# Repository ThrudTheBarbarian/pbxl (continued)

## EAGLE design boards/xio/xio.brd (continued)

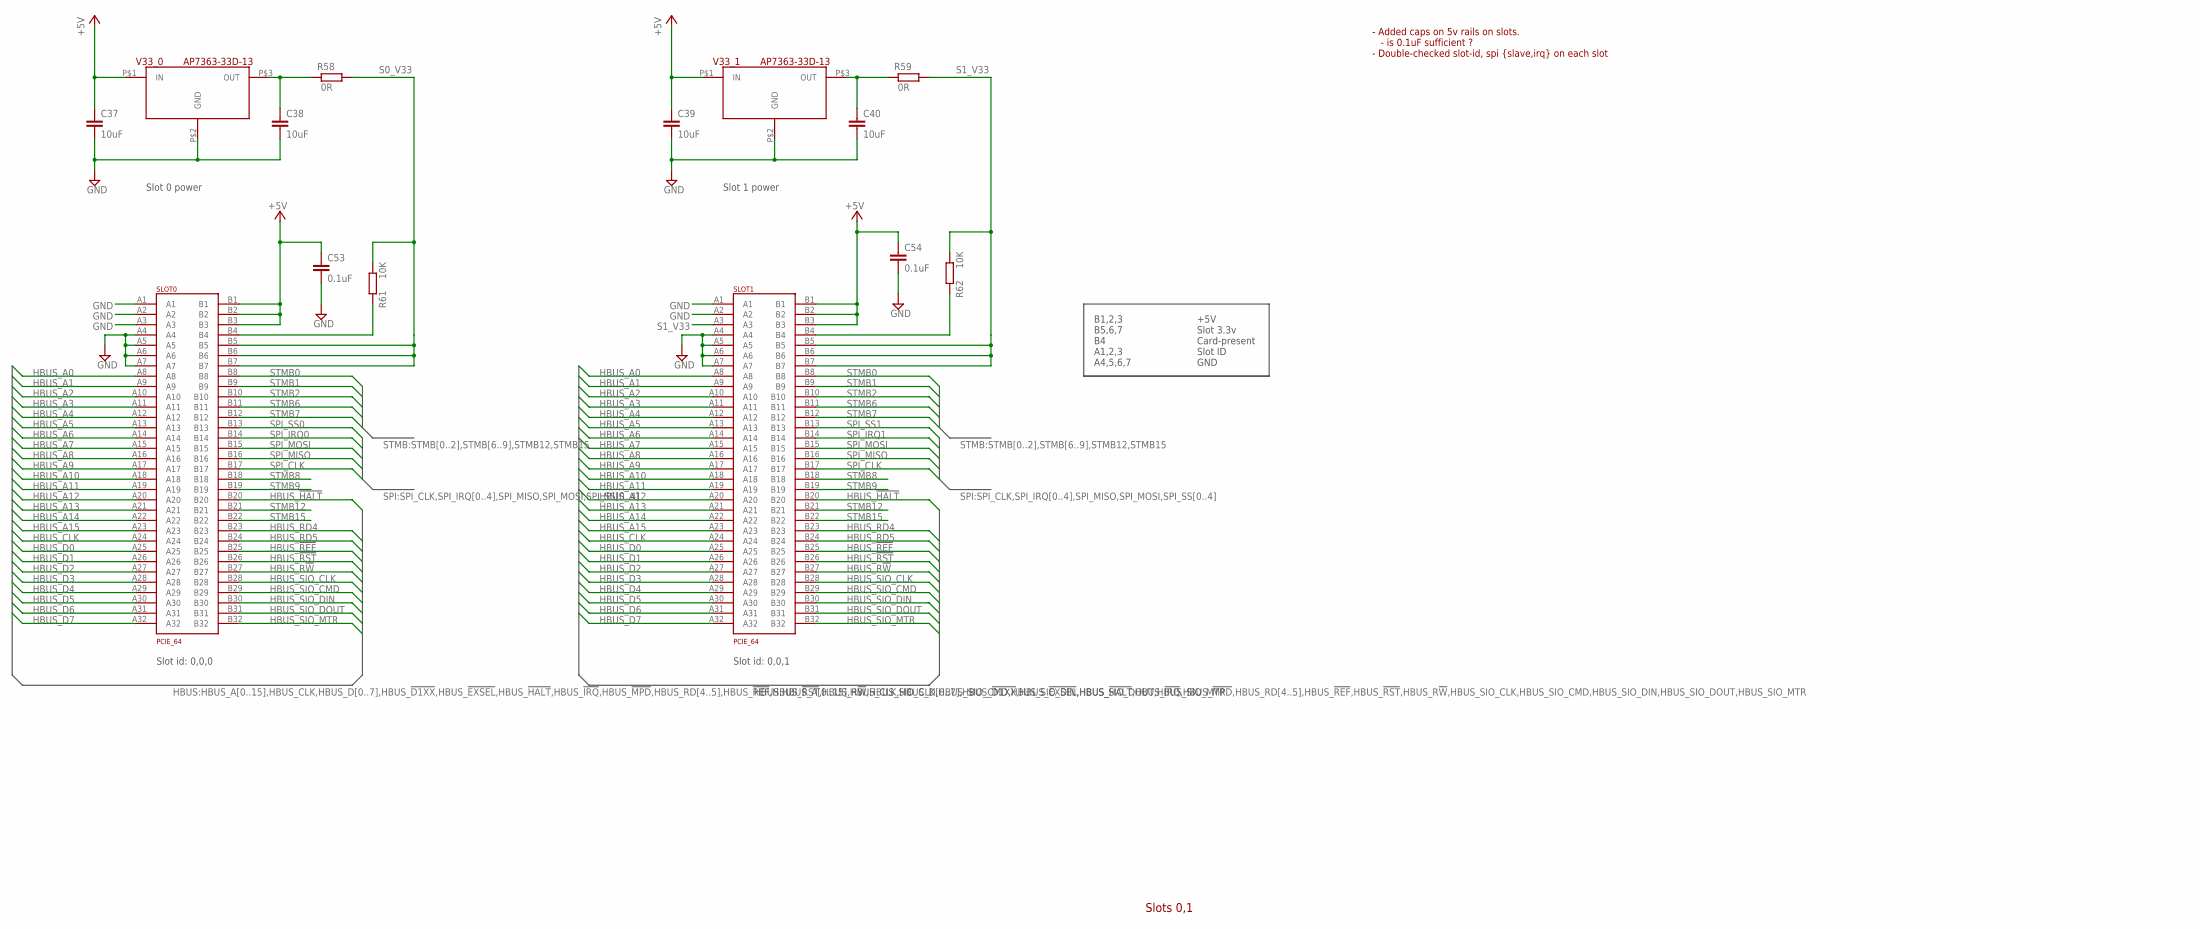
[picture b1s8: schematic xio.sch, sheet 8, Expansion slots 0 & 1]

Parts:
C37, C38, C39, C40: 10uF; C0402K
C53, C54: 0.1uF; C0402K
R58, R59: 0R; R0402
R61, R62: 10K; R0402
SLOT0, SLOT1: PCIE_64; PCI-E_64
V33_0, V33_1: AP7363-33D-13; TO252-3L

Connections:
+5V: C37.1, C39.1, C53.1, C54.1, SLOT0.B1, SLOT0.B2, SLOT0.B3, SLOT1.B1, SLOT1.B2, SLOT1.B3, V33_0.P$1 (IN), V33_1.P$1 (IN); also elsewhere on the board
GND: C37.2, C38.2, C39.2, C40.2, C53.2, C54.2, SLOT0.A1, SLOT0.A2, SLOT0.A3, SLOT0.A4, SLOT0.A5, SLOT0.A6, SLOT0.A7, SLOT1.A1, SLOT1.A2, SLOT1.A4, SLOT1.A5, SLOT1.A6, SLOT1.A7, V33_0.P$2 (GND), V33_1.P$2 (GND); also elsewhere on the board
HBUS_!HALT!: SLOT0.B20, SLOT1.B20; also elsewhere on the board
HBUS_!REF!: SLOT0.B25, SLOT1.B25; also elsewhere on the board
HBUS_!RST!: SLOT0.B26, SLOT1.B26; also elsewhere on the board
HBUS_A0: SLOT0.A8, SLOT1.A8; also elsewhere on the board
HBUS_A1: SLOT0.A9, SLOT1.A9; also elsewhere on the board
HBUS_A2: SLOT0.A10, SLOT1.A10; also elsewhere on the board
HBUS_A3: SLOT0.A11, SLOT1.A11; also elsewhere on the board
HBUS_A4: SLOT0.A12, SLOT1.A12; also elsewhere on the board
HBUS_A5: SLOT0.A13, SLOT1.A13; also elsewhere on the board
HBUS_A6: SLOT0.A14, SLOT1.A14; also elsewhere on the board
HBUS_A7: SLOT0.A15, SLOT1.A15; also elsewhere on the board
HBUS_A8: SLOT0.A16, SLOT1.A16; also elsewhere on the board
HBUS_A9: SLOT0.A17, SLOT1.A17; also elsewhere on the board
HBUS_A10: SLOT0.A18, SLOT1.A18; also elsewhere on the board
HBUS_A11: SLOT0.A19, SLOT1.A19; also elsewhere on the board
HBUS_A12: SLOT0.A20, SLOT1.A20; also elsewhere on the board
HBUS_A13: SLOT0.A21, SLOT1.A21; also elsewhere on the board
HBUS_A14: SLOT0.A22, SLOT1.A22; also elsewhere on the board
HBUS_A15: SLOT0.A23, SLOT1.A23; also elsewhere on the board
HBUS_CLK: SLOT0.A24, SLOT1.A24; also elsewhere on the board
HBUS_D0: SLOT0.A25, SLOT1.A25; also elsewhere on the board
HBUS_D1: SLOT0.A26, SLOT1.A26; also elsewhere on the board
HBUS_D2: SLOT0.A27, SLOT1.A27; also elsewhere on the board
HBUS_D3: SLOT0.A28, SLOT1.A28; also elsewhere on the board
HBUS_D4: SLOT0.A29, SLOT1.A29; also elsewhere on the board
HBUS_D5: SLOT0.A30, SLOT1.A30; also elsewhere on the board
HBUS_D6: SLOT0.A31, SLOT1.A31; also elsewhere on the board
HBUS_D7: SLOT0.A32, SLOT1.A32; also elsewhere on the board
HBUS_R!W!: SLOT0.B27, SLOT1.B27; also elsewhere on the board
HBUS_RD4: SLOT0.B23, SLOT1.B23; also elsewhere on the board
HBUS_RD5: SLOT0.B24, SLOT1.B24; also elsewhere on the board
HBUS_SIO_CLK: SLOT0.B28, SLOT1.B28; also elsewhere on the board
HBUS_SIO_CMD: SLOT0.B29, SLOT1.B29; also elsewhere on the board
HBUS_SIO_DIN: SLOT0.B30, SLOT1.B30; also elsewhere on the board
HBUS_SIO_DOUT: SLOT0.B31, SLOT1.B31; also elsewhere on the board
HBUS_SIO_MTR: SLOT0.B32, SLOT1.B32; also elsewhere on the board
unnamed: R62.2, SLOT1.B4
unnamed: R61.2, SLOT0.B4
unnamed: C38.1, R58.2, V33_0.P$3 (OUT)
unnamed: C40.1, R59.2, V33_1.P$3 (OUT)
S0_V33: R58.1, R61.1, SLOT0.B5, SLOT0.B6, SLOT0.B7
S1_V33: R59.1, R62.1, SLOT1.A3, SLOT1.B5, SLOT1.B6, SLOT1.B7
SPI_CLK: SLOT0.B17, SLOT1.B17; also elsewhere on the board
SPI_IRQ0: SLOT0.B14; also elsewhere on the board
SPI_IRQ1: SLOT1.B14; also elsewhere on the board
SPI_MISO: SLOT0.B16, SLOT1.B16; also elsewhere on the board
SPI_MOSI: SLOT0.B15, SLOT1.B15; also elsewhere on the board
SPI_SS0: SLOT0.B13; also elsewhere on the board
SPI_SS1: SLOT1.B13; also elsewhere on the board
STMB0: SLOT0.B8, SLOT1.B8; also elsewhere on the board
STMB1: SLOT0.B9, SLOT1.B9; also elsewhere on the board
STMB2: SLOT0.B10, SLOT1.B10; also elsewhere on the board
STMB6: SLOT0.B11, SLOT1.B11; also elsewhere on the board
STMB7: SLOT0.B12, SLOT1.B12; also elsewhere on the board
STMB8: SLOT0.B18, SLOT1.B18; also elsewhere on the board
STMB9: SLOT0.B19, SLOT1.B19; also elsewhere on the board
STMB12: SLOT0.B21, SLOT1.B21; also elsewhere on the board
STMB15: SLOT0.B22, SLOT1.B22; also elsewhere on the board

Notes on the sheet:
Slots 0,1
Slot 0 power
Slot 1 power
Slot id: 0,0,0
Slot id: 0,0,1
- Added caps on 5v rails on slots. - is 0.1uF sufficient ? - Double-checked slot-id, spi {slave,irq} on each slot
B1,2,3 B5,6,7 B4 A1,2,3 A4,5,6,7
+5V Slot 3.3v Card-present Slot ID GND

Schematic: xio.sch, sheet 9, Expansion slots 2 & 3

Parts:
C41, C42, C43, C44: 10uF; C0402K
C55, C56: 0.1uF; C0402K
R63, R64: 10K; R0402
R83, R84: 0R; R0402
SLOT2, SLOT3: PCIE_64; PCI-E_64
V33_2, V33_3: AP7363-33D-13; TO252-3L

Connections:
+5V: C41.1, C43.1, C55.1, C56.1, SLOT2.B1, SLOT2.B2, SLOT2.B3, SLOT3.B1, SLOT3.B2, SLOT3.B3, V33_2.P$1 (IN), V33_3.P$1 (IN); also elsewhere on the board
GND: C41.2, C42.2, C43.2, C44.2, C55.2, C56.2, SLOT2.A1, SLOT2.A3, SLOT2.A4, SLOT2.A5, SLOT2.A6, SLOT2.A7, SLOT3.A1, SLOT3.A4, SLOT3.A5, SLOT3.A6, SLOT3.A7, V33_2.P$2 (GND), V33_3.P$2 (GND); also elsewhere on the board
HBUS_!HALT!: SLOT2.B20, SLOT3.B20; also elsewhere on the board
HBUS_!REF!: SLOT2.B25, SLOT3.B25; also elsewhere on the board
HBUS_!RST!: SLOT2.B26, SLOT3.B26; also elsewhere on the board
HBUS_A0: SLOT2.A8, SLOT3.A8; also elsewhere on the board
HBUS_A1: SLOT2.A9, SLOT3.A9; also elsewhere on the board
HBUS_A2: SLOT2.A10, SLOT3.A10; also elsewhere on the board
HBUS_A3: SLOT2.A11, SLOT3.A11; also elsewhere on the board
HBUS_A4: SLOT2.A12, SLOT3.A12; also elsewhere on the board
HBUS_A5: SLOT2.A13, SLOT3.A13; also elsewhere on the board
HBUS_A6: SLOT2.A14, SLOT3.A14; also elsewhere on the board
HBUS_A7: SLOT2.A15, SLOT3.A15; also elsewhere on the board
HBUS_A8: SLOT2.A16, SLOT3.A16; also elsewhere on the board
HBUS_A9: SLOT2.A17, SLOT3.A17; also elsewhere on the board
HBUS_A10: SLOT2.A18, SLOT3.A18; also elsewhere on the board
HBUS_A11: SLOT2.A19, SLOT3.A19; also elsewhere on the board
HBUS_A12: SLOT2.A20, SLOT3.A20; also elsewhere on the board
HBUS_A13: SLOT2.A21, SLOT3.A21; also elsewhere on the board
HBUS_A14: SLOT2.A22, SLOT3.A22; also elsewhere on the board
HBUS_A15: SLOT2.A23, SLOT3.A23; also elsewhere on the board
HBUS_CLK: SLOT2.A24, SLOT3.A24; also elsewhere on the board
HBUS_D0: SLOT2.A25, SLOT3.A25; also elsewhere on the board
HBUS_D1: SLOT2.A26, SLOT3.A26; also elsewhere on the board
HBUS_D2: SLOT2.A27, SLOT3.A27; also elsewhere on the board
HBUS_D3: SLOT2.A28, SLOT3.A28; also elsewhere on the board
HBUS_D4: SLOT2.A29, SLOT3.A29; also elsewhere on the board
HBUS_D5: SLOT2.A30, SLOT3.A30; also elsewhere on the board
HBUS_D6: SLOT2.A31, SLOT3.A31; also elsewhere on the board
HBUS_D7: SLOT2.A32, SLOT3.A32; also elsewhere on the board
HBUS_R!W!: SLOT2.B27, SLOT3.B27; also elsewhere on the board
HBUS_RD4: SLOT2.B23, SLOT3.B23; also elsewhere on the board
HBUS_RD5: SLOT2.B24, SLOT3.B24; also elsewhere on the board
HBUS_SIO_CLK: SLOT2.B28, SLOT3.B28; also elsewhere on the board
HBUS_SIO_CMD: SLOT2.B29, SLOT3.B29; also elsewhere on the board
HBUS_SIO_DIN: SLOT2.B30, SLOT3.B30; also elsewhere on the board
HBUS_SIO_DOUT: SLOT2.B31, SLOT3.B31; also elsewhere on the board
HBUS_SIO_MTR: SLOT2.B32, SLOT3.B32; also elsewhere on the board
unnamed: C42.1, R83.2, V33_2.P$3 (OUT)
unnamed: C44.1, R84.2, V33_3.P$3 (OUT)
unnamed: R63.2, SLOT2.B4
unnamed: R64.2, SLOT3.B4
S2_V33: R63.1, R83.1, SLOT2.A2, SLOT2.B5, SLOT2.B6, SLOT2.B7
S3_V33: R64.1, R84.1, SLOT3.A2, SLOT3.A3, SLOT3.B5, SLOT3.B6, SLOT3.B7
SPI_CLK: SLOT2.B17, SLOT3.B17; also elsewhere on the board
SPI_IRQ2: SLOT2.B14; also elsewhere on the board
SPI_IRQ3: SLOT3.B14; also elsewhere on the board
SPI_MISO: SLOT2.B16, SLOT3.B16; also elsewhere on the board
SPI_MOSI: SLOT2.B15, SLOT3.B15; also elsewhere on the board
SPI_SS2: SLOT2.B13; also elsewhere on the board
SPI_SS3: SLOT3.B13; also elsewhere on the board
STMB0: SLOT2.B8, SLOT3.B8; also elsewhere on the board
STMB1: SLOT2.B9, SLOT3.B9; also elsewhere on the board
STMB2: SLOT2.B10, SLOT3.B10; also elsewhere on the board
STMB6: SLOT2.B11, SLOT3.B11; also elsewhere on the board
STMB7: SLOT2.B12, SLOT3.B12; also elsewhere on the board
STMB8: SLOT2.B18, SLOT3.B18; also elsewhere on the board
STMB9: SLOT2.B19, SLOT3.B19; also elsewhere on the board
STMB12: SLOT2.B21, SLOT3.B21; also elsewhere on the board
STMB15: SLOT2.B22, SLOT3.B22; also elsewhere on the board

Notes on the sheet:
Slot 2 power
Slot 3 power
Slots 2,3
Slot id: 0,1,0
Slot id: 0,1,1
B1,2,3 B5,6,7 B4 A1,2,3 A4,5,6,7
+5V Slot 3.3v Card-present Slot ID GND

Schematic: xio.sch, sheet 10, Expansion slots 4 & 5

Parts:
C45, C46: 10uF; C0402K
C81: 0.1uF; C0402K
R65: 10K; R0402
R85: 0R; R0402
SLOT4: PCIE_64; PCI-E_64
V33_4: AP7363-33D-13; TO252-3L

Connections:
+5V: C45.1, C81.1, SLOT4.B1, SLOT4.B2, SLOT4.B3, V33_4.P$1 (IN); also elsewhere on the board
GND: C45.2, C46.2, C81.2, SLOT4.A2, SLOT4.A3, SLOT4.A4, SLOT4.A5, SLOT4.A6, SLOT4.A7, V33_4.P$2 (GND); also elsewhere on the board
HBUS_!HALT!: SLOT4.B20; also elsewhere on the board
HBUS_!REF!: SLOT4.B25; also elsewhere on the board
HBUS_!RST!: SLOT4.B26; also elsewhere on the board
HBUS_A0: SLOT4.A8; also elsewhere on the board
HBUS_A1: SLOT4.A9; also elsewhere on the board
HBUS_A2: SLOT4.A10; also elsewhere on the board
HBUS_A3: SLOT4.A11; also elsewhere on the board
HBUS_A4: SLOT4.A12; also elsewhere on the board
HBUS_A5: SLOT4.A13; also elsewhere on the board
HBUS_A6: SLOT4.A14; also elsewhere on the board
HBUS_A7: SLOT4.A15; also elsewhere on the board
HBUS_A8: SLOT4.A16; also elsewhere on the board
HBUS_A9: SLOT4.A17; also elsewhere on the board
HBUS_A10: SLOT4.A18; also elsewhere on the board
HBUS_A11: SLOT4.A19; also elsewhere on the board
HBUS_A12: SLOT4.A20; also elsewhere on the board
HBUS_A13: SLOT4.A21; also elsewhere on the board
HBUS_A14: SLOT4.A22; also elsewhere on the board
HBUS_A15: SLOT4.A23; also elsewhere on the board
HBUS_CLK: SLOT4.A24; also elsewhere on the board
HBUS_D0: SLOT4.A25; also elsewhere on the board
HBUS_D1: SLOT4.A26; also elsewhere on the board
HBUS_D2: SLOT4.A27; also elsewhere on the board
HBUS_D3: SLOT4.A28; also elsewhere on the board
HBUS_D4: SLOT4.A29; also elsewhere on the board
HBUS_D5: SLOT4.A30; also elsewhere on the board
HBUS_D6: SLOT4.A31; also elsewhere on the board
HBUS_D7: SLOT4.A32; also elsewhere on the board
HBUS_R!W!: SLOT4.B27; also elsewhere on the board
HBUS_RD4: SLOT4.B23; also elsewhere on the board
HBUS_RD5: SLOT4.B24; also elsewhere on the board
HBUS_SIO_CLK: SLOT4.B28; also elsewhere on the board
HBUS_SIO_CMD: SLOT4.B29; also elsewhere on the board
HBUS_SIO_DIN: SLOT4.B30; also elsewhere on the board
HBUS_SIO_DOUT: SLOT4.B31; also elsewhere on the board
HBUS_SIO_MTR: SLOT4.B32; also elsewhere on the board
unnamed: C46.1, R85.2, V33_4.P$3 (OUT)
unnamed: R65.2, SLOT4.B4
S4_V33: R65.1, R85.1, SLOT4.A1, SLOT4.B5, SLOT4.B6, SLOT4.B7
SPI_CLK: SLOT4.B17; also elsewhere on the board
SPI_IRQ4: SLOT4.B14; also elsewhere on the board
SPI_MISO: SLOT4.B16; also elsewhere on the board
SPI_MOSI: SLOT4.B15; also elsewhere on the board
SPI_SS4: SLOT4.B13; also elsewhere on the board
STMB0: SLOT4.B8; also elsewhere on the board
STMB1: SLOT4.B9; also elsewhere on the board
STMB2: SLOT4.B10; also elsewhere on the board
STMB6: SLOT4.B11; also elsewhere on the board
STMB7: SLOT4.B12; also elsewhere on the board
STMB8: SLOT4.B18; also elsewhere on the board
STMB9: SLOT4.B19; also elsewhere on the board
STMB12: SLOT4.B21; also elsewhere on the board
STMB15: SLOT4.B22; also elsewhere on the board

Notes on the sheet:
Slots 4,5
Slot 4 power
Slot id: 1,0,0
B1,2,3 B5,6,7 B4 A1,2,3 A4,5,6,7
+5V Slot 3.3v Card-present Slot ID GND

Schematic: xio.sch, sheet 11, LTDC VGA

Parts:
D1, D2, D3, D4, D5: BAT54S; SOT23
Q1, Q2: BSS138; SOT23
R10, R28, R42: 71.5K; R0402
R13, R29, R43: 35.7K; R0402
R19, R30, R44: 17.8K; R0402
R20, R31, R45: 8.66K; R0402
R22, R32, R46: 4.37K; R0402
R23, R33, R47: 2.18K; R0402
R24, R34, R48: 1.05K; R0402
R25, R35, R49: 549R; R0402
R50, R51: 1K; R0402
VGA: ICD15S13E4GX00LF; DB15
VGA_BLU: SN74ALVC244PWR; TSSOP20
VGA_GRN: SN74ALVC244PWR; TSSOP20
VGA_RED: SN74ALVC244PWR; TSSOP20
XIO: STM32F429B-XIO; PQFP208

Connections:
+3V3: D3.2 (C2), D4.2 (C2), D5.2 (C2), Q1.1 (G), Q2.1 (G), VGA_BLU.20 (VCC), VGA_GRN.20 (VCC), VGA_RED.20 (VCC); also elsewhere on the board
+5V: D1.2 (C2), D2.2 (C2), R50.1, R51.1; also elsewhere on the board
GND: D1.1 (A1), D2.1 (A1), D3.1 (A1), D4.1 (A1), D5.1 (A1), VGA.5, VGA.6, VGA.7, VGA.8, VGA.10, VGA_BLU.1 (!A_OE!), VGA_BLU.10 (GND), VGA_BLU.19 (!B_OE!), VGA_GRN.1 (!A_OE!), VGA_GRN.10 (GND), VGA_GRN.19 (!B_OE!), VGA_RED.1 (!A_OE!), VGA_RED.10 (GND), VGA_RED.19 (!B_OE!); also elsewhere on the board
LCD_B0: VGA_BLU.2 (A0), XIO.174 (PJ12)
LCD_B1: VGA_BLU.4 (A1), XIO.175 (PJ13)
LCD_B2: VGA_BLU.6 (A2), XIO.176 (PJ14)
LCD_B3: VGA_BLU.8 (A3), XIO.177 (PJ15)
LCD_B4: VGA_BLU.11 (B0), XIO.186 (PK3)
LCD_B5: VGA_BLU.13 (B1), XIO.187 (PK4)
LCD_B6: VGA_BLU.15 (B2), XIO.188 (PK5)
LCD_B7: VGA_BLU.17 (B3), XIO.189 (PK6)
LCD_G0: VGA_GRN.2 (A0), XIO.119 (PJ7)
LCD_G1: VGA_GRN.4 (A1), XIO.120 (PJ8)
LCD_G2: VGA_GRN.6 (A2), XIO.121 (PJ9)
LCD_G3: VGA_GRN.8 (A3), XIO.122 (PJ10)
LCD_G4: VGA_GRN.11 (B0), XIO.123 (PJ11)
LCD_G5: VGA_GRN.13 (B1), XIO.126 (PK0)
LCD_G6: VGA_GRN.15 (B2), XIO.127 (PK1)
LCD_G7: VGA_GRN.17 (B3), XIO.128 (PK2)
LCD_HS: Q2.2 (S), XIO.20 (PI13)
LCD_R0: VGA_RED.2 (A0), XIO.64 (PI15)
LCD_R1: VGA_RED.4 (A1), XIO.65 (PJ0)
LCD_R2: VGA_RED.6 (A2), XIO.66 (PJ1)
LCD_R3: VGA_RED.8 (A3), XIO.67 (PJ2)
LCD_R4: VGA_RED.11 (B0), XIO.68 (PJ3)
LCD_R5: VGA_RED.13 (B1), XIO.69 (PJ4)
LCD_R6: VGA_RED.15 (B2), XIO.95 (PJ5)
LCD_R7: VGA_RED.17 (B3), XIO.118 (PJ6)
LCD_VS: Q1.2 (S), XIO.19 (PI12)
unnamed: R10.2, VGA_RED.18 (Y0)
unnamed: R13.2, VGA_RED.16 (Y1)
unnamed: R19.2, VGA_RED.14 (Y2)
unnamed: R20.2, VGA_RED.12 (Y3)
unnamed: R22.2, VGA_RED.9 (Z0)
unnamed: R23.2, VGA_RED.7 (Z1)
unnamed: R24.2, VGA_RED.5 (Z2)
unnamed: R25.2, VGA_RED.3 (Z3)
unnamed: R35.2, VGA_GRN.3 (Z3)
unnamed: R34.2, VGA_GRN.5 (Z2)
unnamed: R33.2, VGA_GRN.7 (Z1)
unnamed: R32.2, VGA_GRN.9 (Z0)
unnamed: R31.2, VGA_GRN.12 (Y3)
unnamed: R30.2, VGA_GRN.14 (Y2)
unnamed: R29.2, VGA_GRN.16 (Y1)
unnamed: R28.2, VGA_GRN.18 (Y0)
unnamed: R49.2, VGA_BLU.3 (Z3)
unnamed: R48.2, VGA_BLU.5 (Z2)
unnamed: R47.2, VGA_BLU.7 (Z1)
unnamed: R46.2, VGA_BLU.9 (Z0)
unnamed: R45.2, VGA_BLU.12 (Y3)
unnamed: R44.2, VGA_BLU.14 (Y2)
unnamed: R43.2, VGA_BLU.16 (Y1)
unnamed: R42.2, VGA_BLU.18 (Y0)
VGA_B: D3.3 (C1A2), R42.1, R43.1, R44.1, R45.1, R46.1, R47.1, R48.1, R49.1, VGA.3
VGA_G: D4.3 (C1A2), R28.1, R29.1, R30.1, R31.1, R32.1, R33.1, R34.1, R35.1, VGA.2
VGA_HS: D1.3 (C1A2), Q2.3 (D), R51.2, VGA.13
VGA_R: D5.3 (C1A2), R10.1, R13.1, R19.1, R20.1, R22.1, R23.1, R24.1, R25.1, VGA.1
VGA_VS: D2.3 (C1A2), Q1.3 (D), R50.2, VGA.14

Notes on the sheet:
LCD to VGA

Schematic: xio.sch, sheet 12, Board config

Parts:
ARCH_ID: 209-4MS; EDG-04
MEM_ID: 209-2MS; EDG-02
PID: 209-3MS; EDG-03
R6, R7, R8, R9, R14, R15, R16, R17, R18: 47K; R0402
XIO: STM32F429B-XIO; PQFP208

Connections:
+3V3: ARCH_ID.5, ARCH_ID.6, ARCH_ID.7, ARCH_ID.8, MEM_ID.3, MEM_ID.4, PID.4, PID.5, PID.6; also elsewhere on the board
ARCH0: ARCH_ID.1, R9.1, XIO.129 (PG2)
ARCH1: ARCH_ID.2, R8.1, XIO.130 (PG3)
ARCH2: ARCH_ID.3, R7.1, XIO.133 (PG6)
ARCH3: ARCH_ID.4, R6.1, XIO.134 (PG7)
GND: R6.2, R7.2, R8.2, R9.2, R14.2, R15.2, R16.2, R17.2, R18.2; also elsewhere on the board
MEM0: MEM_ID.1, R18.1, XIO.179 (PG10)
MEM1: MEM_ID.2, R17.1, XIO.180 (PG11)
PID0: PID.1, R16.1, XIO.7 (PI8)
PID1: PID.2, R15.1, XIO.13 (PI11)
PID2: PID.3, R14.1, XIO.21 (PI14)

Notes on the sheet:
Architecture selection
Peripheral-ID selection
Memory-emulation selection
Board config

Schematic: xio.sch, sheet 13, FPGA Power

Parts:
C36, C47, C48, C49, C50, C51, C58, C59, C74, C75, C77, C80, C84, C87: 4.7uF; C0402K
C52, C73, C76, C78, C79, C82, C83, C85, C86, C88: 0.47uF; C0402K
C93: 10uF; C0402K
C95: 0.1uF; C0402K
R67: 120R; R0402
VREG1_2: LD1117; SOT223
XLX-: 6SLX9TQG144; TQ144

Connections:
1.2V: C36.1, C73.1, C74.1, C75.1, C93.1, R67.1, VREG1_2.2 (VOUT), VREG1_2.4 (TAB), XLX-.P19 (VCCINT), XLX-.P28 (VCCINT), XLX-.P52 (VCCINT), XLX-.P89 (VCCINT), XLX-.P128 (VCCINT)
+3V3: C47.1, C48.1, C49.1, C50.1, C51.1, C52.1, C58.1, C59.1, C76.1, C77.1, C78.1, C79.1, C80.1, C82.1, C83.1, C84.1, C85.1, C86.1, C87.1, C88.1, C95.1, VREG1_2.3 (VIN), XLX-.P20 (VCCAUX), XLX-.P36 (VCCAUX), XLX-.P53 (VCCAUX), XLX-.P90 (VCCAUX), XLX-.P129 (VCCAUX); also elsewhere on the board
GND: C36.2, C47.2, C48.2, C49.2, C50.2, C51.2, C52.2, C58.2, C59.2, C73.2, C74.2, C75.2, C76.2, C77.2, C78.2, C79.2, C80.2, C82.2, C83.2, C84.2, C85.2, C86.2, C87.2, C88.2, C93.2, C95.2, R67.2, VREG1_2.1 (GND), XLX-.P3 (GND), XLX-.P13 (GND), XLX-.P25 (GND), XLX-.P49 (GND), XLX-.P54 (GND), XLX-.P68 (GND), XLX-.P77 (GND), XLX-.P91 (GND), XLX-.P96 (GND), XLX-.P108 (GND), XLX-.P113 (GND), XLX-.P130 (GND), XLX-.P136 (GND); also elsewhere on the board

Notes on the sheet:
VccAux bypass caps
VccInt bypass caps
VccO bank 0
VccO bank 1
VccO bank 2
VccO bank 3
Bypass cap number and capacitance taken from ug393

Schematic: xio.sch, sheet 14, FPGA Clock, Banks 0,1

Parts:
C35: 0.01uF; C0402K
J1: 12401598E4#2A; AMPHENOL_12401598E4#2A
JP1: PINHD-2X8; 2X08
JP2: PINHD-2X7; 2X07
OSC1: ASEMB-50.000MHZ-LC-T; OSC_3.2X2.5MM
R78, R79, R80, R81, R82, R86, R87: 33R; R0402
XLX-: 6SLX9TQG144; TQ144

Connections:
+3V3: C35.1, JP1.15, JP2.14, OSC1.4 (VCC), XLX-.P76 (VCCO_1), XLX-.P86 (VCCO_1), XLX-.P103 (VCCO_1), XLX-.P122 (VCCO_0), XLX-.P125 (VCCO_0), XLX-.P135 (VCCO_0); also elsewhere on the board
FBUS0: JP1.14, XLX-.P127 (IO_L36P_GCLK15_0)
FBUS1: JP1.12, XLX-.P126 (IO_L36N_GCLK14_0)
FBUS2: JP1.10, XLX-.P123 (IO_L37N_GCLK12_0)
FBUS3: JP1.8, XLX-.P121 (IO_L62P_0)
FBUS4: JP1.6, XLX-.P120 (IO_L62N_VREF_0)
FBUS5: JP1.4, XLX-.P119 (IO_L63P_SCP7_0)
FBUS6: JP1.2, XLX-.P118 (IO_L63N_SCP6_0)
FBUS7: JP1.13, XLX-.P117 (IO_L64P_SCP5_0)
FBUS8: JP1.11, XLX-.P116 (IO_L64N_SCP4_0)
FBUS9: JP1.9, XLX-.P115 (IO_L65P_SCP3_0)
FBUS10: JP1.7, XLX-.P114 (IO_L65N_SCP2_0)
FBUS11: JP1.5, XLX-.P112 (IO_L66P_SCP1_0)
FBUS12: JP1.3, XLX-.P111 (IO_L66N_SCP0_0)
FBUS13: JP2.1, XLX-.P105 (IO_L1P_1)
FBUS14: JP2.3, XLX-.P104 (IO_L1N_VREF_1)
FBUS15: JP2.5, XLX-.P99 (IO_L33N_1)
FBUS16: JP2.7, XLX-.P98 (IO_L34P_1)
FBUS17: JP2.9, XLX-.P97 (IO_L34N_1)
FBUS18: JP2.11, XLX-.P95 (IO_L40P_GCLK11_1)
FBUS19: JP2.2, XLX-.P88 (IO_L42P_GCLK7_1)
FBUS20: JP2.4, XLX-.P87 (IO_L42N_GCLK6_TRDY1_1)
FBUS21: JP2.6, XLX-.P85 (IO_L43P_GCLK5_1)
FBUS22: JP2.8, XLX-.P84 (IO_L43N_GCLK4_1)
FBUS23: JP2.10, XLX-.P83 (IO_L45P_1)
FBUS24: JP2.12, XLX-.P82 (IO_L45N_1)
GND: C35.2, J1.A1 (GND), J1.A12 (GND), J1.B1 (GND), J1.B12 (GND), J1.SH1 (SHIELD), J1.SH2 (SHIELD), J1.SH3 (SHIELD), J1.SH4 (SHIELD), JP1.1, JP1.16, JP2.13, OSC1.2 (GND), XLX-.P144 (IO_L1P_HSWAPEN_0); also elsewhere on the board
HBUS_DDIR: XLX-.P143 (IO_L1N_VREF_0); also elsewhere on the board
LX_CLK: OSC1.3 (OUT), XLX-.P124 (IO_L37P_GCLK13_0)
LX_RC_N: J1.B10 (SSRXN1), XLX-.P131 (IO_L35N_GCLK16_0)
LX_RC_P: J1.B11 (SSRXP1), XLX-.P132 (IO_L35P_GCLK17_0)
LX_RD_N: J1.B2 (SSTXP2), XLX-.P141 (IO_L2N_0)
LX_RD_P: J1.B3 (SSTXN2), XLX-.P142 (IO_L2P_0)
LX_TC_N: J1.A6 (DP1), XLX-.P137 (IO_L4N_0)
LX_TC_P: J1.A7 (DN1), XLX-.P138 (IO_L4P_0)
LX_TD0_N: J1.A2 (SSTXP1), XLX-.P133 (IO_L34N_GCLK18_0)
LX_TD0_P: J1.A3 (SSTXN1), XLX-.P134 (IO_L34P_GCLK19_0)
LX_TD1_N: J1.A10 (SSRXN2), XLX-.P139 (IO_L3N_0)
LX_TD1_P: J1.A11 (SSRXP2), XLX-.P140 (IO_L3P_0)
unnamed: R82.1, XLX-.P92 (IO_L41N_GCLK8_1)
unnamed: R81.1, XLX-.P94 (IO_L40N_GCLK10_1)
unnamed: R79.1, XLX-.P100 (IO_L33P_1)
unnamed: R78.1, XLX-.P101 (IO_L32N_1)
unnamed: R80.1, XLX-.P75 (IO_L74P_AWAKE_1)
unnamed: R86.1, XLX-.P81 (IO_L46P_1)
unnamed: R87.1, XLX-.P79 (IO_L47P_1)
XSPI_1_MISO: R80.2; also elsewhere on the board
XSPI_1_MOSI: XLX-.P74 (IO_L74N_DOUT_BUSY_1); also elsewhere on the board
XSPI_1_SCK: XLX-.P78 (IO_L47N_1); also elsewhere on the board
XSPI_3_MISO: XLX-.P93 (IO_L41P_GCLK9_IRDY1_1); also elsewhere on the board
XSPI_3_MOSI: R82.2; also elsewhere on the board
XSPI_3_SCK: R81.2; also elsewhere on the board
XSPI_5_MISO: XLX-.P80 (IO_L46N_1); also elsewhere on the board
XSPI_5_MOSI: R87.2; also elsewhere on the board
XSPI_5_SCK: R86.2; also elsewhere on the board
XSPI_6_MISO: XLX-.P102 (IO_L32P_1); also elsewhere on the board
XSPI_6_MOSI: R79.2; also elsewhere on the board
XSPI_6_SCK: R78.2; also elsewhere on the board

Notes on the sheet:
INH can be left floating for normal operation
Trace thickness Prepreg thickness Trace width Inter-trace spacing Prepreg dielectric Differential impedance
0.035 mm 0.12 mm 10 mil 7 mil 4.4 90.5 ohms
USB3 connections
Bank 0
Bank 1
Clock
FPGA Clock, Banks 0 & 1

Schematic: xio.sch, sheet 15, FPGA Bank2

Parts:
A_MUX: TS3A27518EPWR; TSSOP24
C25, C30, C96: 0.1uF; C0402K
C97: 1uF; C0402K
FPGA_CFG: W25Q80DVSNIG; SOIC8_150MIL
FPGA_DONE: LTST-C191KFKT; CHIPLED_0603
FPGA_PROG: XILINX-JTAG; 332-14
R52: 680R; R0402
R54, R55, R57: 2.4K; R0402
R60, R66, R70, R71: 4.7K; R0402
R68, R69: 33R; R0402
RESET_XLX: 1825910-6; TACTILE-PTH
XLX-: 6SLX9TQG144; TQ144

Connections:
+3V3: A_MUX.8 (VCC), A_MUX.16 (NO6), A_MUX.18 (NO5), C25.1, C96.1, C97.1, FPGA_CFG.8 (VCC), FPGA_PROG.2 (VREF), R52.1, R54.2, R55.2, R57.2, R60.2, R66.2, XLX-.P42 (VCCO_2), XLX-.P63 (VCCO_2), XLX-.P69 (IO_L1N_M0_CMPMISO_2); also elsewhere on the board
FLASH_CLK: A_MUX.2 (NC1), R68.2
FLASH_CS: A_MUX.21 (NC4), R57.1, XLX-.P38 (IO_L65N_CSO_B_2)
FLASH_D0: A_MUX.1 (NC2), R69.2
FLASH_D1: A_MUX.23 (NC3), XLX-.P65 (IO_L3P_D0_DIN_MISO_MISO1_2)
FLASH_D2: A_MUX.19 (NC5), R55.1, XLX-.P62 (IO_L12P_D1_MISO2_2)
FLASH_D3: A_MUX.22 (NC6), R54.1, XLX-.P61 (IO_L12N_D2_MISO3_2)
GND: A_MUX.5 (GND), A_MUX.17 (NO4), C25.2, C30.2, C96.2, C97.2, FPGA_CFG.4 (VSS), FPGA_DONE.C, FPGA_PROG.1 (GND), FPGA_PROG.3 (GND), FPGA_PROG.5 (GND), FPGA_PROG.7 (GND), FPGA_PROG.9 (GND), FPGA_PROG.11 (GND), FPGA_PROG.13 (GND), R70.2, R71.2, RESET_XLX.1, RESET_XLX.2, XLX-.P60 (IO_L13P_M1_2), XLX-.P73 (SUSPEND); also elsewhere on the board
HBUS_!CCTL!: XLX-.P40 (IO_L64N_D9_2); also elsewhere on the board
HBUS_!REF!: XLX-.P44 (IO_L62P_D5_2); also elsewhere on the board
HBUS_!RST!: XLX-.P45 (IO_L49N_D4_2); also elsewhere on the board
HBUS_!S4!: XLX-.P47 (IO_L48N_RDWR_B_VREF_2); also elsewhere on the board
HBUS_!S5!: XLX-.P48 (IO_L48P_D7_2); also elsewhere on the board
HBUS_R!W!: XLX-.P46 (IO_L49P_D3_2); also elsewhere on the board
HBUS_RD4: XLX-.P41 (IO_L64P_D8_2); also elsewhere on the board
HBUS_RD5: XLX-.P43 (IO_L62N_D6_2); also elsewhere on the board
HBUS_SIO_CLK: XLX-.P50 (IO_L31N_GCLK30_D15_2); also elsewhere on the board
HBUS_SIO_CMD: XLX-.P51 (IO_L31P_GCLK31_D14_2); also elsewhere on the board
HBUS_SIO_DIN: XLX-.P55 (IO_L30N_GCLK0_USERCCLK_2); also elsewhere on the board
HBUS_SIO_DOUT: XLX-.P56 (IO_L30P_GCLK1_D13_2); also elsewhere on the board
HBUS_SIO_MTR: XLX-.P57 (IO_L14N_D12_2); also elsewhere on the board
unnamed: A_MUX.4 (COM1), FPGA_CFG.6 (SCK)
unnamed: FPGA_DONE.A, R52.2, XLX-.P71 (DONE_2)
unnamed: R60.1, XLX-.P39 (IO_L65P_INIT_B_2)
unnamed: C30.1, R66.1, RESET_XLX.3, RESET_XLX.4, XLX-.P37 (PROGRAM_B_2)
unnamed: FPGA_PROG.4 (SS/PROG/TMS), XLX-.P107 (TMS)
unnamed: FPGA_PROG.6 (SCK/CCLK/TCK), XLX-.P109 (TCK)
unnamed: FPGA_PROG.8 (MISO/DONE/TDO), XLX-.P106 (TDO)
unnamed: FPGA_PROG.10 (MOSI/DIN/TDI), XLX-.P110 (TDI)
unnamed: A_MUX.6 (COM2), FPGA_CFG.5 (MOSI)
unnamed: A_MUX.7 (COM3), FPGA_CFG.2 (MISO)
unnamed: A_MUX.9 (COM4), FPGA_CFG.1 (SSEL)
unnamed: A_MUX.10 (COM5), FPGA_CFG.3 (#WP/IO2)
unnamed: A_MUX.12 (COM6), FPGA_CFG.7 (#HOLD/IO3)
unnamed: R68.1, XLX-.P70 (IO_L1P_CCLK_2)
unnamed: R69.1, XLX-.P64 (IO_L3N_MOSI_CSI_B_MISO0_2)
unnamed: A_MUX.20 (!EN!), R70.1
SPI_CLK: A_MUX.11 (NO1); also elsewhere on the board
SPI_MISO: A_MUX.15 (NO3); also elsewhere on the board
SPI_MOSI: A_MUX.13 (NO2); also elsewhere on the board
SPI_MUX_IN: A_MUX.14 (IN2), A_MUX.24 (IN1), R71.1; also elsewhere on the board

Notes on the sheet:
Green LED
Bank 2 / Config
CMPCS_B for Xilinx use only
Trace thickness Prepreg thickness Trace width Prepreg dielectric Trace impedance
0.035 mm 0.12 mm 8 mil 4.4 50.2 ohms
FLASH_CLK impedance matching
Place 33R resistors close to FPGA pins
Default (NC) is that the FPGA has control over the SPI flash. If the STM pulls XIO_MUX_EN high, it gains control
Pins 12,14 are NC

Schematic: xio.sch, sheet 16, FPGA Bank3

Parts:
C57, C60, C61, C62, C63, C64, C65, C66, C67, C68, C69, C70, C71, C72: 0.1uF; C0402K
CARTRIDGE: A8_CART
LVL_AHI: SN74LVC8T245; TSSOP24
LVL_ALO: SN74LVC8T245; TSSOP24
LVL_CLK: 74LVCH1T45GW,125; SOT363
LVL_D: SN74LVC8T245; TSSOP24
LVL_RD4, LVL_RD5: 74LVCH1T45GW,125; SOT363
LVL_RW: 74LVCH1T45GW,125; SOT363
XLX-: 6SLX9TQG144; TQ144

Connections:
+3V3: C57.1, C60.1, C61.1, C62.1, C63.1, C64.1, C65.1, LVL_AHI.1 (VCCA), LVL_AHI.2 (DIR), LVL_ALO.1 (VCCA), LVL_ALO.2 (DIR), LVL_CLK.1 (VCCA), LVL_CLK.5 (DIR), LVL_D.1 (VCCA), LVL_RD4.5 (DIR), LVL_RD4.6 (VCCB), LVL_RD5.5 (DIR), LVL_RD5.6 (VCCB), LVL_RW.1 (VCCA), LVL_RW.5 (DIR), XLX-.P4 (VCCO_3), XLX-.P18 (VCCO_3), XLX-.P31 (VCCO_3); also elsewhere on the board
+5V: C66.1, C67.1, C68.1, C69.1, C70.1, C71.1, C72.1, CARTRIDGE.P13 (VCC5), LVL_AHI.23 (VCCB), LVL_AHI.24 (VCCB), LVL_ALO.23 (VCCB), LVL_ALO.24 (VCCB), LVL_CLK.6 (VCCB), LVL_D.23 (VCCB), LVL_D.24 (VCCB), LVL_RD4.1 (VCCA), LVL_RD5.1 (VCCA), LVL_RW.6 (VCCB); also elsewhere on the board
CBUS_!CCTL!: CARTRIDGE.P15 (!CCTL!), LVL_AHI.16 (B6)
CBUS_!S4!: CARTRIDGE.P1 (!S4!), LVL_AHI.15 (B7)
CBUS_!S5!: CARTRIDGE.P12 (!S5!), LVL_AHI.14 (B8)
CBUS_A0: CARTRIDGE.P5 (A0), LVL_ALO.21 (B1)
CBUS_A1: CARTRIDGE.P4 (A1), LVL_ALO.20 (B2)
CBUS_A2: CARTRIDGE.P3 (A2), LVL_ALO.19 (B3)
CBUS_A3: CARTRIDGE.P2 (A3), LVL_ALO.18 (B4)
CBUS_A4: CARTRIDGE.PC (A4), LVL_ALO.17 (B5)
CBUS_A5: CARTRIDGE.PD (A5), LVL_ALO.16 (B6)
CBUS_A6: CARTRIDGE.PE (A6), LVL_ALO.15 (B7)
CBUS_A7: CARTRIDGE.PF (A7), LVL_ALO.14 (B8)
CBUS_A8: CARTRIDGE.PH (A8), LVL_AHI.21 (B1)
CBUS_A9: CARTRIDGE.PJ (A9), LVL_AHI.20 (B2)
CBUS_A10: CARTRIDGE.PP (A10), LVL_AHI.19 (B3)
CBUS_A11: CARTRIDGE.PN (A11), LVL_AHI.18 (B4)
CBUS_A12: CARTRIDGE.PK (A12), LVL_AHI.17 (B5)
CBUS_B02: CARTRIDGE.PS (B02), LVL_CLK.4 (B)
CBUS_D0: CARTRIDGE.P10 (D0), LVL_D.21 (B1)
CBUS_D1: CARTRIDGE.P9 (D1), LVL_D.20 (B2)
CBUS_D2: CARTRIDGE.P8 (D2), LVL_D.19 (B3)
CBUS_D3: CARTRIDGE.PL (D3), LVL_D.18 (B4)
CBUS_D4: CARTRIDGE.P6 (D4), LVL_D.17 (B5)
CBUS_D5: CARTRIDGE.P7 (D5), LVL_D.16 (B6)
CBUS_D6: CARTRIDGE.P11 (D6), LVL_D.15 (B7)
CBUS_D7: CARTRIDGE.PM (D7), LVL_D.14 (B8)
CBUS_R/!W!: CARTRIDGE.PR (R/!W!), LVL_RW.4 (B)
GND: C57.2, C60.2, C61.2, C62.2, C63.2, C64.2, C65.2, C66.2, C67.2, C68.2, C69.2, C70.2, C71.2, C72.2, CARTRIDGE.PB (GND), LVL_AHI.11 (GND), LVL_AHI.12 (GND), LVL_AHI.13 (GND), LVL_AHI.22 (!OE!), LVL_ALO.11 (GND), LVL_ALO.12 (GND), LVL_ALO.13 (GND), LVL_ALO.22 (!OE!), LVL_CLK.2 (GND), LVL_D.11 (GND), LVL_D.12 (GND), LVL_D.13 (GND), LVL_D.22 (!OE!), LVL_RD4.2 (GND), LVL_RD5.2 (GND), LVL_RW.2 (GND); also elsewhere on the board
HBUS_!CCTL!: LVL_AHI.8 (A6); also elsewhere on the board
HBUS_!S4!: LVL_AHI.9 (A7); also elsewhere on the board
HBUS_!S5!: LVL_AHI.10 (A8); also elsewhere on the board
HBUS_A0: LVL_ALO.3 (A1), XLX-.P22 (IO_L42P_GCLK25_TRDY2_3); also elsewhere on the board
HBUS_A1: LVL_ALO.4 (A2), XLX-.P21 (IO_L42N_GCLK24_3); also elsewhere on the board
HBUS_A2: LVL_ALO.5 (A3), XLX-.P17 (IO_L43P_GCLK23_3); also elsewhere on the board
HBUS_A3: LVL_ALO.6 (A4), XLX-.P16 (IO_L43N_GCLK22_IRDY2_3); also elsewhere on the board
HBUS_A4: LVL_ALO.7 (A5), XLX-.P15 (IO_L44P_GCLK21_3); also elsewhere on the board
HBUS_A5: LVL_ALO.8 (A6), XLX-.P14 (IO_L44N_GCLK20_3); also elsewhere on the board
HBUS_A6: LVL_ALO.9 (A7), XLX-.P12 (IO_L49P_3); also elsewhere on the board
HBUS_A7: LVL_ALO.10 (A8), XLX-.P11 (IO_L49N_3); also elsewhere on the board
HBUS_A8: LVL_AHI.3 (A1), XLX-.P29 (IO_L36N_3); also elsewhere on the board
HBUS_A9: LVL_AHI.4 (A2), XLX-.P27 (IO_L37P_3); also elsewhere on the board
HBUS_A10: LVL_AHI.5 (A3), XLX-.P26 (IO_L37N_3); also elsewhere on the board
HBUS_A11: LVL_AHI.6 (A4), XLX-.P24 (IO_L41P_GCLK27_3); also elsewhere on the board
HBUS_A12: LVL_AHI.7 (A5), XLX-.P23 (IO_L41N_GCLK26_3); also elsewhere on the board
HBUS_A13: XLX-.P33 (IO_L2P_3); also elsewhere on the board
HBUS_A14: XLX-.P32 (IO_L2N_3); also elsewhere on the board
HBUS_A15: XLX-.P30 (IO_L36P_3); also elsewhere on the board
HBUS_CLK: LVL_CLK.3 (A), XLX-.P34 (IO_L1N_VREF_3); also elsewhere on the board
HBUS_D0: LVL_D.3 (A1), XLX-.P10 (IO_L50P_3); also elsewhere on the board
HBUS_D1: LVL_D.4 (A2), XLX-.P9 (IO_L50N_3); also elsewhere on the board
HBUS_D2: LVL_D.5 (A3), XLX-.P8 (IO_L51P_3); also elsewhere on the board
HBUS_D3: LVL_D.6 (A4), XLX-.P7 (IO_L51N_3); also elsewhere on the board
HBUS_D4: LVL_D.7 (A5), XLX-.P6 (IO_L52P_3); also elsewhere on the board
HBUS_D5: LVL_D.8 (A6), XLX-.P5 (IO_L52N_3); also elsewhere on the board
HBUS_D6: LVL_D.9 (A7), XLX-.P2 (IO_L83P_3); also elsewhere on the board
HBUS_D7: LVL_D.10 (A8), XLX-.P1 (IO_L83N_VREF_3); also elsewhere on the board
HBUS_DDIR: LVL_D.2 (DIR); also elsewhere on the board
HBUS_R!W!: LVL_RW.3 (A); also elsewhere on the board
HBUS_RD4: LVL_RD4.4 (B); also elsewhere on the board
HBUS_RD5: LVL_RD5.4 (B); also elsewhere on the board
unnamed: CARTRIDGE.PA (RD4), LVL_RD4.3 (A)
unnamed: CARTRIDGE.P14 (RD5), LVL_RD5.3 (A)

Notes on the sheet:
Dir=high : A->B tPD_AB : 0.7 .. 4.4ns tPD_BA : 0.6 .. 5.4ns
74LVCH1T45GW:
SN74LVC8T245:
Dir=high : A->B tPD_AB : 0.5 .. 4.4ns tPD_BA : 0.6 .. 6ns

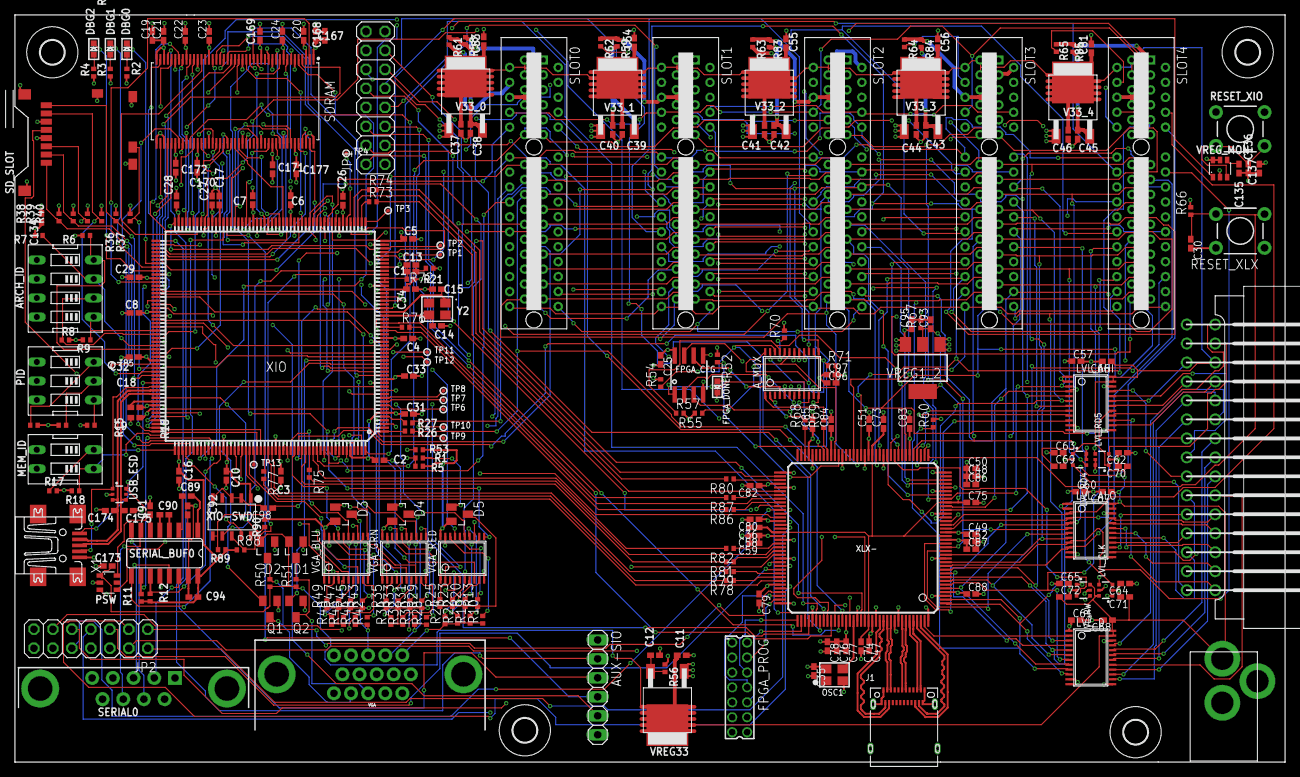
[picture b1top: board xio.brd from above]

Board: 6 copper layers, 170.0 x 100.0 mm, 280 parts (0 on the bottom side), 378 nets.
